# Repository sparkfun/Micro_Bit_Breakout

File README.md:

SparkFun micro:bit Breakout Board
========================================

[*Micro Bit Breakout (BOB-16446)*](https://www.sparkfun.com/products/16446)

The [Micro Bit Breakout](https://www.sparkfun.com/products/16446) is a board that connects to the BBC micro:bit and breaks out all 21 GPIO pins, power, and ground to a 0.1" header. It expands the capabilities of the micro:bit by providing access to more pins and allowing for connections to the I<sup>2</sup>C and SPI buses. It additionally has two qwiic connectors to take advantage of the Qwiic I2C protocols. 

The micro:bit Breakout Board is also [available without pre-soldered headers](https://www.sparkfun.com/products/16445). More information can be found in the [Micro Bit Breakout Hookup Guide](https://learn.sparkfun.com/tutorials/microbit-breakout-board-hookup-guide).

Repository Contents
-------------------

* **/Documentation** - Data sheets, additional product information
* **/Firmware** - Example code used with micro:bit and the breakout board. MakeCode examples are compiled HEX codes and can be modified once they are imported into MakeCode editor. MicroPython examples can also be modified in a Python editor like Mu.
* **/Hardware** - Eagle design files (.brd, .sch)
* **/Production** - Production panel files (.brd)

Documentation
--------------
* Tutorials
  * **[Hookup Guide](https://learn.sparkfun.com/tutorials/microbit-breakout-board-hookup-guide)** - Basic hookup guide.
  * **[SparkFun Inventor's Kit for micro:bit Experiment Guide](https://learn.sparkfun.com/tutorials/sparkfun-inventors-kit-for-microbit-experiment-guide)** - Experiment Guide
  * **[micro:bit Educator Lab Pack Experiment Guide](https://learn.sparkfun.com/tutorials/microbit-educator-lab-pack-experiment-guide)** - Experiment Guide for the Lab Pack
  * **[Getting Started with MicroPython and the SparkFun Inventor's Kit for micro:bit](https://learn.sparkfun.com/tutorials/getting-started-with-micropython-and-the-sparkfun-inventors-kit-for-microbit)** Experiment Guide in MicroPython
* **[SparkFun Fritzing repo](https://github.com/sparkfun/Fritzing_Parts)** - Fritzing diagrams for SparkFun products.
* **[SparkFun 3D Model repo](https://github.com/sparkfun/3D_Models)** - 3D models of SparkFun products. 
* **[SparkFun Graphical Datasheets](https://github.com/sparkfun/Graphical_Datasheets)** -Graphical Datasheets for various SparkFun products.

Product Versions
----------------
* [Micro Bit Breakout v0.3 (BOB-16446)](https://www.sparkfun.com/products/16446) - v0.3
* [Micro Bit Breakout (Without Headers) v0.3 (BOB-16445)](https://www.sparkfun.com/products/16445) - v0.3
* [Micro Bit Breakout v0.2 (BOB-13988)](https://www.sparkfun.com/products/13988) - Initial release
* [Micro Bit Breakout v0.2 with Headers (BOB-13989)](https://www.sparkfun.com/products/13989) - Initial release

Version History
---------------
* [v03](https://github.com/sparkfun/Micro_Bit_Breakout/tree/v03) - v0.3 Changed connector to SMD, added Qwiic connectors
* [v02](https://github.com/sparkfun/Micro_Bit_Breakout/tree/v02) - v0.2 Increased board width, changed pin numbers
* [v01](https://github.com/sparkfun/Micro_Bit_Breakout/tree/v01) - v0.1 Hardware release

License Information
-------------------

This product is _**open source**_! 

Please review the LICENSE.md file for license information. 

If you have any questions or concerns on licensing, please contact techsupport@sparkfun.com.

Distributed as-is; no warranty is given.

- Your friends at SparkFun.

_<COLLABORATION CREDIT>_

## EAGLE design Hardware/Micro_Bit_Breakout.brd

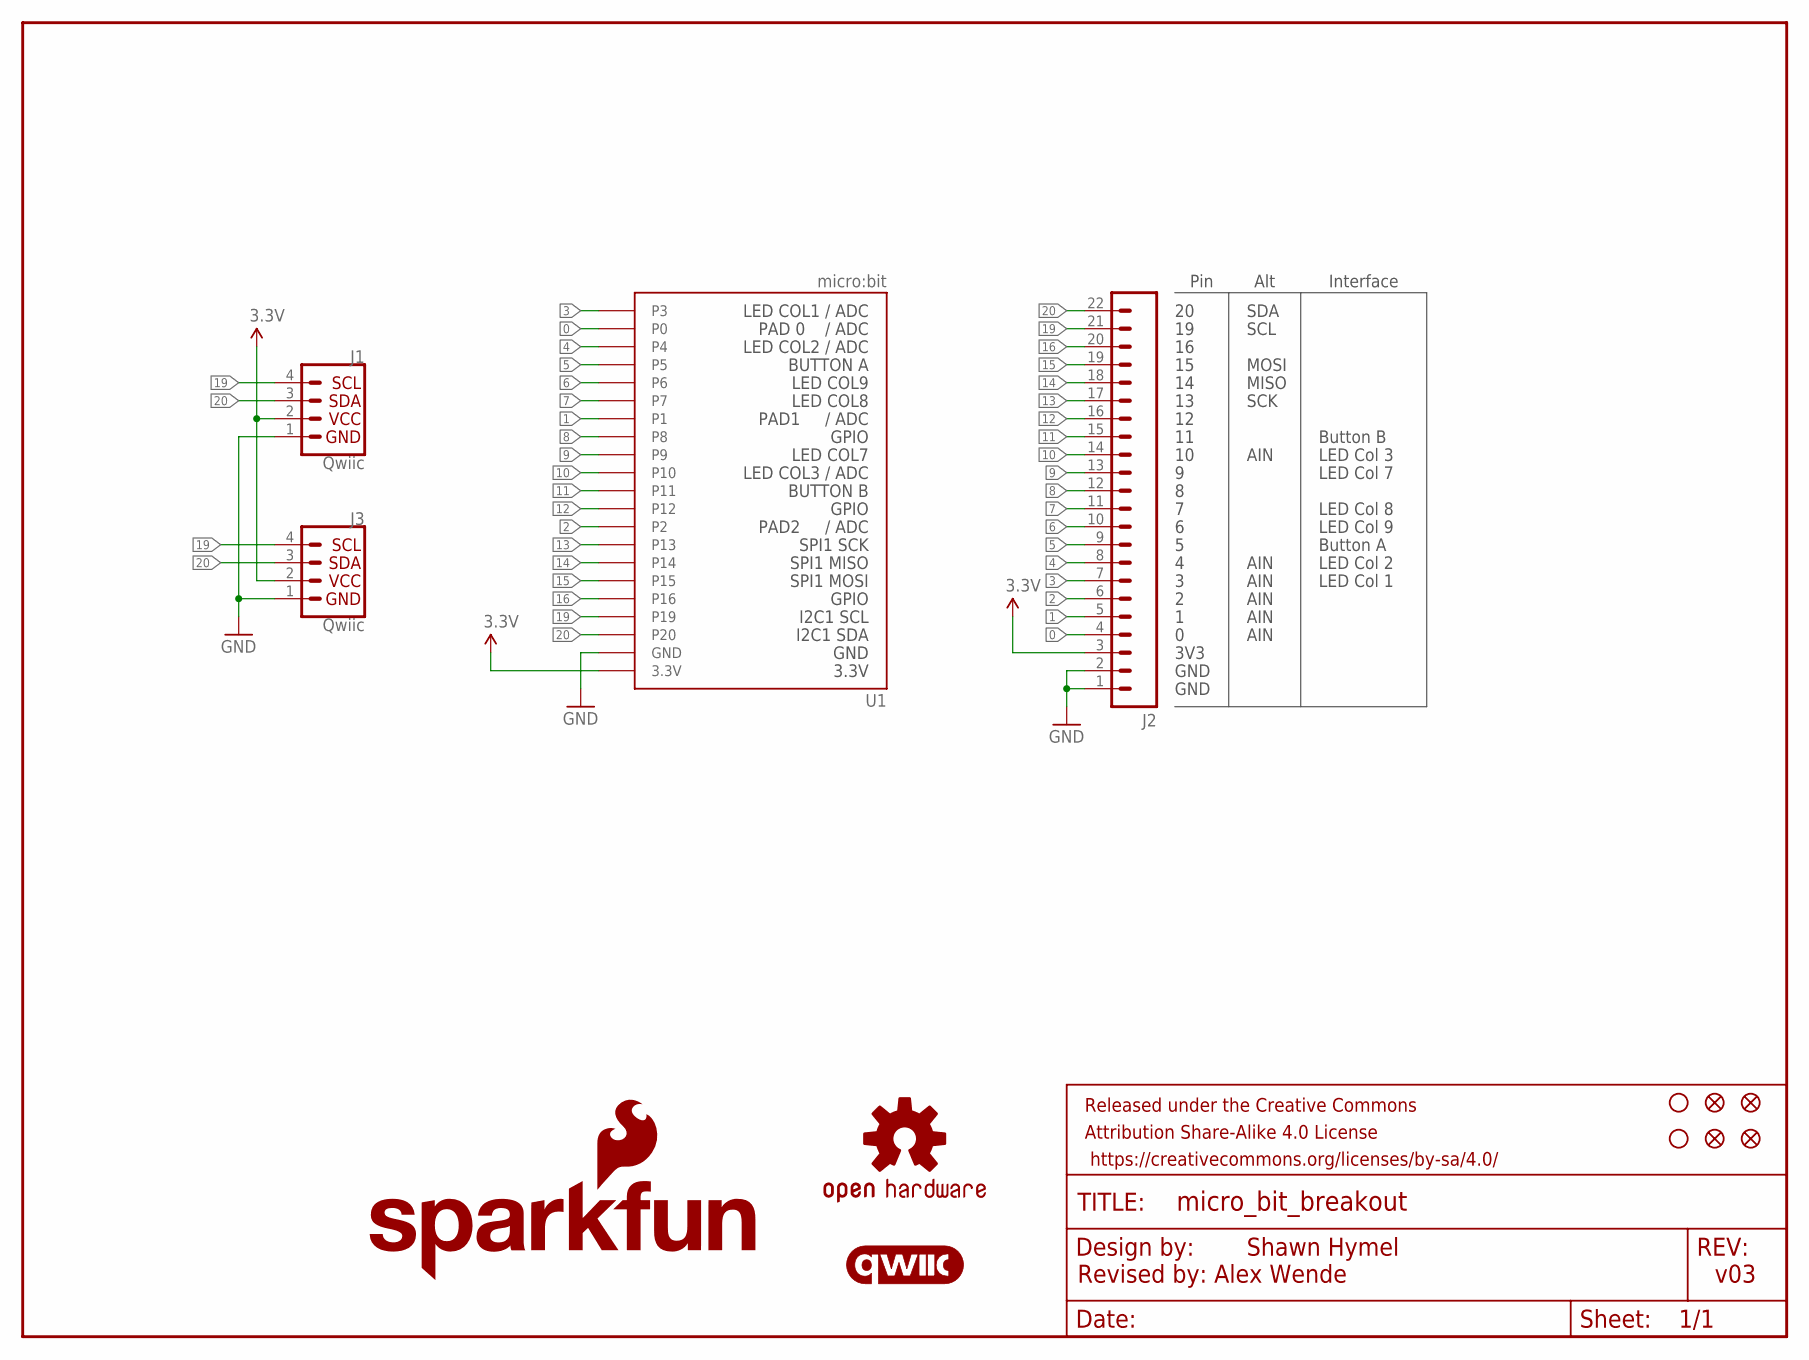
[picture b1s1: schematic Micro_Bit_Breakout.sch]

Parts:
FD1, FD2, FD3, FD4: FIDUCIAL1X2; FIDUCIAL-1X2
FRAME1: FRAME-LETTER; CREATIVE_COMMONS
H1, H2: STAND-OFF
J1, J3: Qwiic; JST04_1MM_VERT
J2: CONN_22_NOSILK; 1X22_NOSILK
LOGO1: QWIIC_LOGO_5MM; QWIIC_5MM
LOGO2: SFE_LOGO_NAME_FLAME.1_INCH; SFE_LOGO_NAME_FLAME_.1
LOGO3: OSHW-LOGOM; OSHW-LOGO-M
U1: micro:bit; MICRO:BIT-RA_SMD

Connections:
0: J2.4, U1.P$2 (P0), U1.P$3 (P0), U1.P$4 (P0), U1.P$5 (P0)
1: J2.5, U1.P$10 (P1), U1.P$11 (P1), U1.P$12 (P1), U1.P$13 (P1)
2: J2.6, U1.P$19 (P2), U1.P$20 (P2), U1.P$21 (P2), U1.P$22 (P2)
3: J2.7, U1.P$1 (P3)
3.3V: J1.2, J2.3, J3.2, U1.P$27 (3.3V), U1.P$28 (3.3V), U1.P$29 (3.3V), U1.P$30 (3.3V), U1.P$31 (3.3V), U1.P$32 (3.3V)
4: J2.8, U1.P$6 (P4)
5: J2.9, U1.P$7 (P5)
6: J2.10, U1.P$8 (P6)
7: J2.11, U1.P$9 (P7)
8: J2.12, U1.P$14 (P8)
9: J2.13, U1.P$15 (P9)
10: J2.14, U1.P$16 (P10)
11: J2.15, U1.P$17 (P11)
12: J2.16, U1.P$18 (P12)
13: J2.17, U1.P$23 (P13)
14: J2.18, U1.P$24 (P14)
15: J2.19, U1.P$25 (P15)
16: J2.20, U1.P$26 (P16)
19: J1.4, J2.21, J3.4, U1.P$33 (P19)
20: J1.3, J2.22, J3.3, U1.P$34 (P20)
GND: J1.1, J2.1, J2.2, J3.1, U1.P$35 (GND), U1.P$36 (GND), U1.P$37 (GND), U1.P$38 (GND), U1.P$39 (GND), U1.P$40 (GND)

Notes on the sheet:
Shawn Hymel
v03
GND
3V3
SCL
SDA
SCK
MISO
MOSI
AIN
Button B
LED Col 3
LED Col 7
LED Col 8
LED Col 9
LED Col 2
Button A
LED Col 1
Pin
Alt
Interface
Revised by: Alex Wende

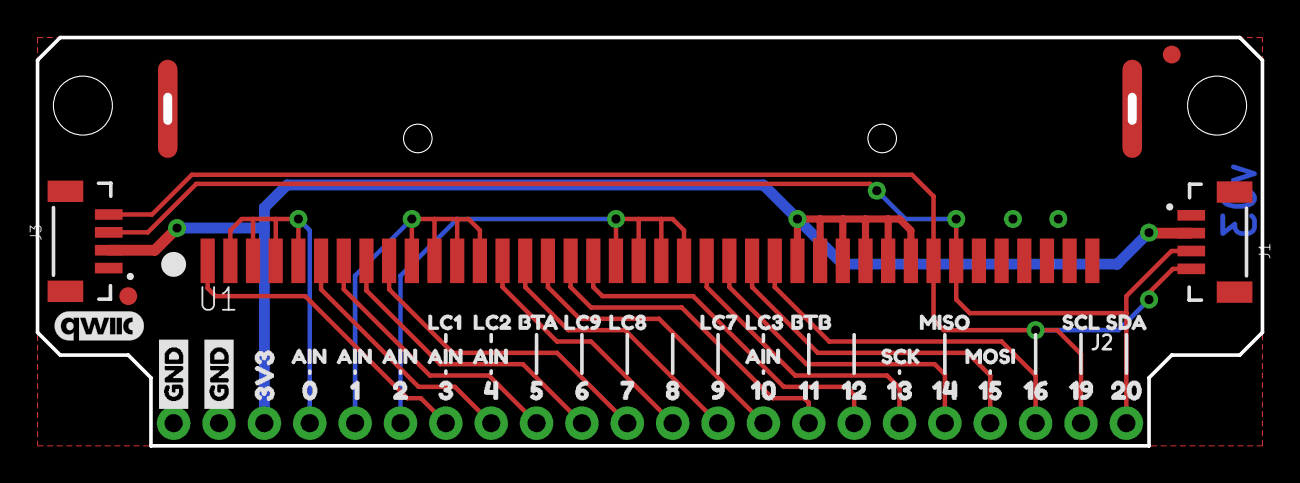
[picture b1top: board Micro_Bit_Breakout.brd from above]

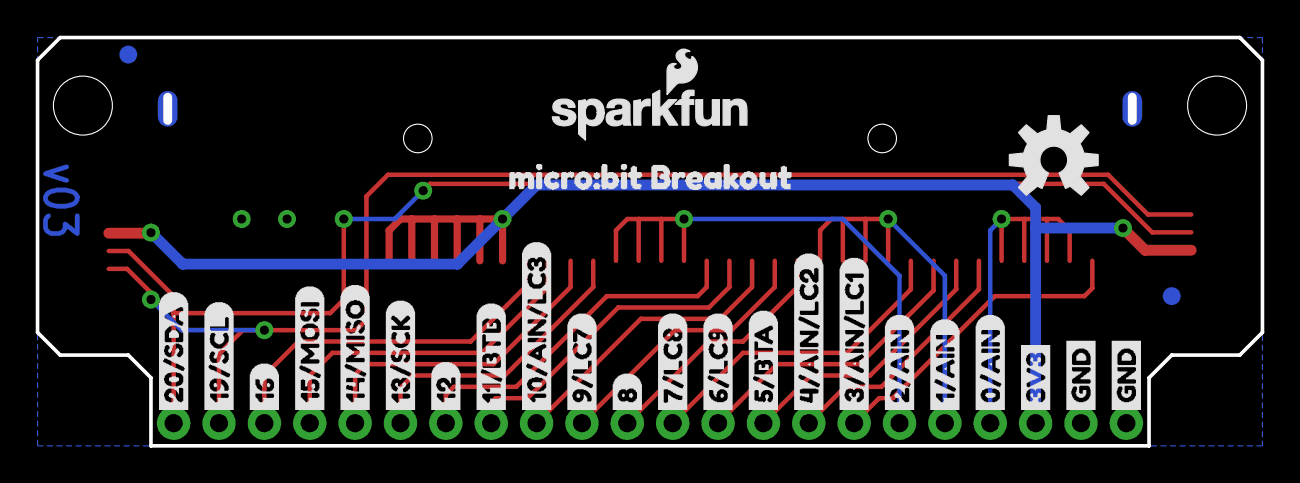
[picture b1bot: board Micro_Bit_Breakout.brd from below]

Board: 2 copper layers, 68.3 x 22.6 mm, 78 parts (27 on the bottom side), 21 nets.

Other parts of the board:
U$1, U$22, U$23, U$24: GND0
U$2: 20#SDA20
U$3: 19#SCL19
U$4, U$43: 1618
U$5: 15#MOSI17
U$6: 14#MISO16
U$7: 13#SCK15
U$8, U$39: 1214
U$9: 11#BTB13
U$10: 10#AIN#LC312
U$11: 9#LC711
U$12, U$35: 810
U$13: 7#LC89
U$14: 6#LC98
U$15: 5#BTA7
U$16: 4#AIN#LC26
U$17: 3#AIN#LC15
U$18: 2#AIN4
U$19: 1#AIN3
U$20: 0#AIN2
U$21, U$26: 3V31
U$25: MICRO#BIT_BREAKOUT0
U$27: 02
U$28: 13
U$29: 24
U$30: 35
U$31: 46
U$32: 57
U$33: 68
U$34: 79
U$36: 911
U$37: 1012
U$38: 1113
U$40: 1315
U$41: 1416
U$42: 1517
U$44: 1919
U$45: 2020
U$46, U$47, U$48, U$49, U$50, U$51: AIN0
U$52: LC11
U$53: LC22
U$54: BTA3
U$55: LC95
U$56: LC86
U$57: LC77
U$58: LC38
U$59: BTB4
U$60: SCK9
U$61: MISO10
U$62: MOSI11
U$63: SCL12
U$64: SDA13

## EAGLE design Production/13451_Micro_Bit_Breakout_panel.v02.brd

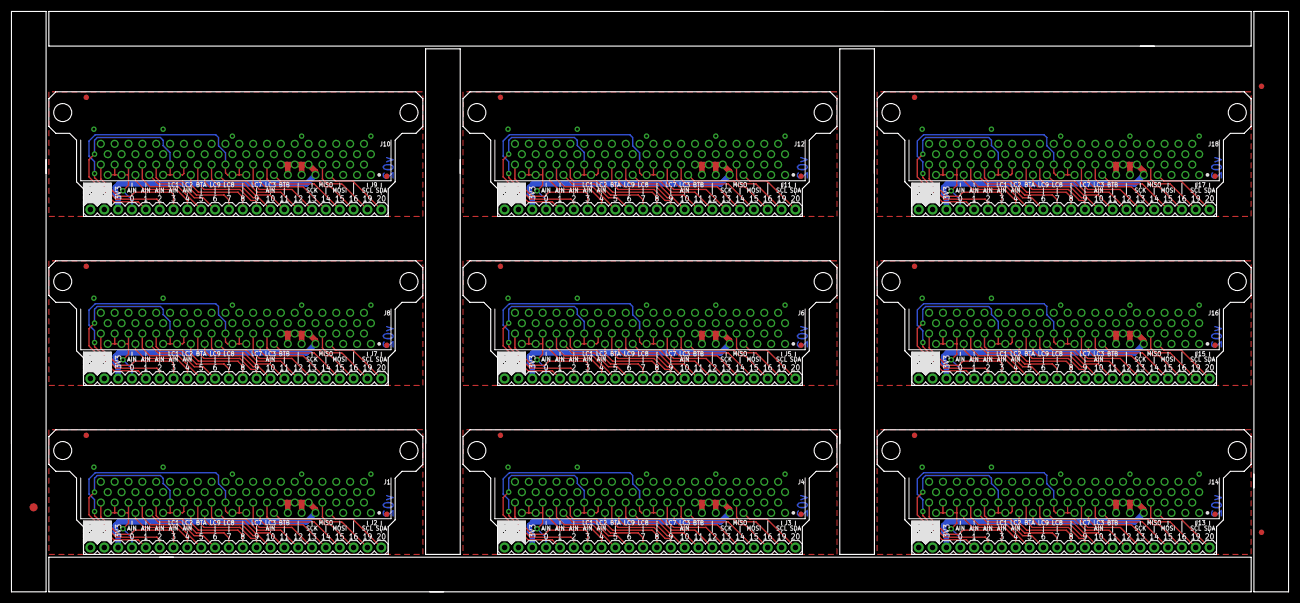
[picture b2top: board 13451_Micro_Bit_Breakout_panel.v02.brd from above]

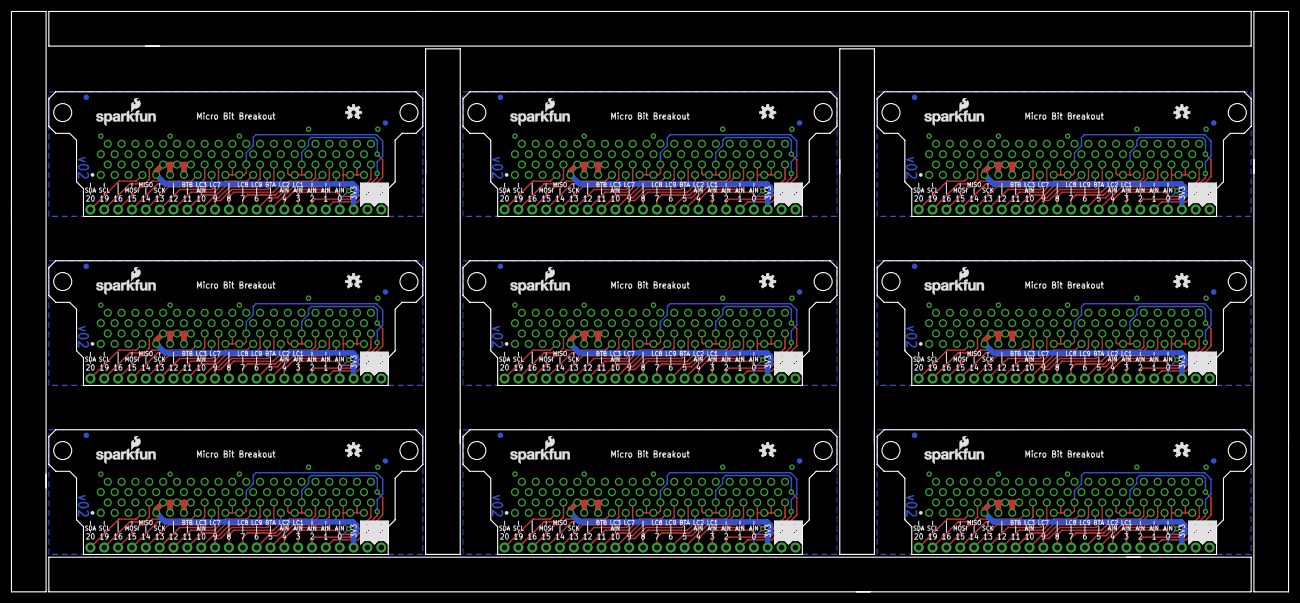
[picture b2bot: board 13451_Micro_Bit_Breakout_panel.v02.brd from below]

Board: 2 copper layers, 234.2 x 106.4 mm, 111 parts (45 on the bottom side), 189 nets.

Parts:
E$1: FIDUCIAL-1.5X3
E$9, E$10: FIDUCIAL-1X2
FD1, FD2, FD3, FD4, FD5, FD6, FD7, FD8, FD9, FD10, FD11, FD12, FD13, FD14, FD15, FD16, FD17, FD18, FD19, FD20, FD21, FD22, FD23, FD24, FD25, FD26, FD27, FD28, FD29, FD30, FD31, FD32, FD33, FD34, FD35, FD36: FIDUCIAL1X2; FIDUCIAL-1X2
H1, H2, H3, H4, H5, H6, H7, H8, H9, H10, H11, H12, H13, H14, H15, H16, H17, H18: STAND-OFF
J1, J4, J6, J8, J10, J12, J14, J16, J18: EDGE-80PTH-RA; VEC-127-080-R
J2, J3, J5, J7, J9, J11, J13, J15, J17: M22PTH; 1X22
LOGO1, LOGO3, LOGO5, LOGO7, LOGO9, LOGO11, LOGO13, LOGO15, LOGO17: OSHW-LOGOS; OSHW-LOGO-S
LOGO2, LOGO4, LOGO6, LOGO8, LOGO10, LOGO12, LOGO14, LOGO16, LOGO18: SFE_LOGO_NAME_FLAME.1_INCH; SFE_LOGO_NAME_FLAME_.1
U$1, U$2, U$3, U$4, U$5, U$6, U$7, U$8, U$9, U$10, U$11, U$12, U$13, U$14, U$15, U$16, U$17, U$18: NEGASILK_MICRO_BIT_BREAKOUT

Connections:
0: J1.A36, J1.A37, J1.A38, J1.A39, J2.4
1: J1.A28, J1.A29, J1.A30, J1.A31, J2.5
2: J1.A19, J1.A20, J1.A21, J1.A22, J2.6
3: J1.A40, J2.7
3.3V: J1.A9, J1.A10, J1.A11, J1.A12, J1.A13, J1.A14, J2.3
3.3V1: J3.3, J4.A9, J4.A10, J4.A11, J4.A12, J4.A13, J4.A14
3.3V2: J5.3, J6.A9, J6.A10, J6.A11, J6.A12, J6.A13, J6.A14
3.3V3: J7.3, J8.A9, J8.A10, J8.A11, J8.A12, J8.A13, J8.A14
3.3V4: J9.3, J10.A9, J10.A10, J10.A11, J10.A12, J10.A13, J10.A14
3.3V5: J11.3, J12.A9, J12.A10, J12.A11, J12.A12, J12.A13, J12.A14
3.3V6: J13.3, J14.A9, J14.A10, J14.A11, J14.A12, J14.A13, J14.A14
3.3V7: J15.3, J16.A9, J16.A10, J16.A11, J16.A12, J16.A13, J16.A14
3.3V8: J17.3, J18.A9, J18.A10, J18.A11, J18.A12, J18.A13, J18.A14
4: J1.A35, J2.8
5: J1.A34, J2.9
6: J1.A33, J2.10
7: J1.A32, J2.11
8: J1.A27, J2.12
9: J1.A26, J2.13
10: J1.A25, J2.14
11: J1.A24, J2.15
12: J1.A23, J2.16
13: J1.A18, J2.17
14: J1.A17, J2.18
15: J1.A16, J2.19
16: J1.A15, J2.20
17: J3.22, J4.A7
18: J3.21, J4.A8
19: J1.A8, J2.21
20: J1.A7, J2.22
21: J3.20, J4.A15
22: J3.19, J4.A16
23: J3.18, J4.A17
24: J3.17, J4.A18
25: J3.6, J4.A19, J4.A20, J4.A21, J4.A22
26: J3.16, J4.A23
27: J3.15, J4.A24
28: J3.14, J4.A25
29: J3.13, J4.A26
30: J3.12, J4.A27
31: J3.5, J4.A28, J4.A29, J4.A30, J4.A31
32: J3.11, J4.A32
33: J3.10, J4.A33
34: J3.9, J4.A34
35: J3.8, J4.A35
36: J3.4, J4.A36, J4.A37, J4.A38, J4.A39
37: J3.7, J4.A40
38: J5.22, J6.A7
39: J5.21, J6.A8
40: J5.20, J6.A15
41: J5.19, J6.A16
42: J5.18, J6.A17
43: J5.17, J6.A18
44: J5.6, J6.A19, J6.A20, J6.A21, J6.A22
45: J5.16, J6.A23
46: J5.15, J6.A24
47: J5.14, J6.A25
48: J5.13, J6.A26
49: J5.12, J6.A27
50: J5.5, J6.A28, J6.A29, J6.A30, J6.A31
51: J5.11, J6.A32
52: J5.10, J6.A33
53: J5.9, J6.A34
54: J5.8, J6.A35
55: J5.4, J6.A36, J6.A37, J6.A38, J6.A39
56: J5.7, J6.A40
57: J7.22, J8.A7
58: J7.21, J8.A8
59: J7.20, J8.A15
60: J7.19, J8.A16
61: J7.18, J8.A17
62: J7.17, J8.A18
63: J7.6, J8.A19, J8.A20, J8.A21, J8.A22
64: J7.16, J8.A23
65: J7.15, J8.A24
66: J7.14, J8.A25
67: J7.13, J8.A26
68: J7.12, J8.A27
69: J7.5, J8.A28, J8.A29, J8.A30, J8.A31
70: J7.11, J8.A32
71: J7.10, J8.A33
72: J7.9, J8.A34
73: J7.8, J8.A35
74: J7.4, J8.A36, J8.A37, J8.A38, J8.A39
75: J7.7, J8.A40
76: J9.22, J10.A7
77: J9.21, J10.A8
78: J9.20, J10.A15
79: J9.19, J10.A16
80: J9.18, J10.A17
81: J9.17, J10.A18
82: J9.6, J10.A19, J10.A20, J10.A21, J10.A22
83: J9.16, J10.A23
84: J9.15, J10.A24
85: J9.14, J10.A25
86: J9.13, J10.A26
87: J9.12, J10.A27
88: J9.5, J10.A28, J10.A29, J10.A30, J10.A31
89: J9.11, J10.A32
90: J9.10, J10.A33
91: J9.9, J10.A34
92: J9.8, J10.A35
93: J9.4, J10.A36, J10.A37, J10.A38, J10.A39
94: J9.7, J10.A40
95: J11.22, J12.A7
96: J11.21, J12.A8
97: J11.20, J12.A15
98: J11.19, J12.A16
99: J11.18, J12.A17
100: J11.17, J12.A18
101: J11.6, J12.A19, J12.A20, J12.A21, J12.A22
102: J11.16, J12.A23
103: J11.15, J12.A24
104: J11.14, J12.A25
105: J11.13, J12.A26
106: J11.12, J12.A27
107: J11.5, J12.A28, J12.A29, J12.A30, J12.A31
108: J11.11, J12.A32
109: J11.10, J12.A33
110: J11.9, J12.A34
111: J11.8, J12.A35
112: J11.4, J12.A36, J12.A37, J12.A38, J12.A39
113: J11.7, J12.A40
114: J13.22, J14.A7
115: J13.21, J14.A8
116: J13.20, J14.A15
117: J13.19, J14.A16
118: J13.18, J14.A17
119: J13.17, J14.A18
120: J13.6, J14.A19, J14.A20, J14.A21, J14.A22
121: J13.16, J14.A23
122: J13.15, J14.A24
123: J13.14, J14.A25
124: J13.13, J14.A26
125: J13.12, J14.A27
126: J13.5, J14.A28, J14.A29, J14.A30, J14.A31
127: J13.11, J14.A32
128: J13.10, J14.A33
129: J13.9, J14.A34
130: J13.8, J14.A35
131: J13.4, J14.A36, J14.A37, J14.A38, J14.A39
132: J13.7, J14.A40
133: J15.22, J16.A7
134: J15.21, J16.A8
135: J15.20, J16.A15
136: J15.19, J16.A16
137: J15.18, J16.A17
138: J15.17, J16.A18
139: J15.6, J16.A19, J16.A20, J16.A21, J16.A22
140: J15.16, J16.A23
141: J15.15, J16.A24
142: J15.14, J16.A25
143: J15.13, J16.A26
144: J15.12, J16.A27
145: J15.5, J16.A28, J16.A29, J16.A30, J16.A31
146: J15.11, J16.A32
147: J15.10, J16.A33
148: J15.9, J16.A34
149: J15.8, J16.A35
150: J15.4, J16.A36, J16.A37, J16.A38, J16.A39
151: J15.7, J16.A40
152: J17.22, J18.A7
153: J17.21, J18.A8
154: J17.20, J18.A15
155: J17.19, J18.A16
156: J17.18, J18.A17
157: J17.17, J18.A18
158: J17.6, J18.A19, J18.A20, J18.A21, J18.A22
159: J17.16, J18.A23
160: J17.15, J18.A24
161: J17.14, J18.A25
162: J17.13, J18.A26
163: J17.12, J18.A27
164: J17.5, J18.A28, J18.A29, J18.A30, J18.A31
165: J17.11, J18.A32
166: J17.10, J18.A33
167: J17.9, J18.A34
168: J17.8, J18.A35
169: J17.4, J18.A36, J18.A37, J18.A38, J18.A39
170: J17.7, J18.A40
GND: J1.A1, J1.A2, J1.A3, J1.A4, J1.A5, J1.A6, J2.1, J2.2
GND1: J3.1, J3.2, J4.A1, J4.A2, J4.A3, J4.A4, J4.A5, J4.A6
GND2: J5.1, J5.2, J6.A1, J6.A2, J6.A3, J6.A4, J6.A5, J6.A6
GND3: J7.1, J7.2, J8.A1, J8.A2, J8.A3, J8.A4, J8.A5, J8.A6
GND4: J9.1, J9.2, J10.A1, J10.A2, J10.A3, J10.A4, J10.A5, J10.A6
GND5: J11.1, J11.2, J12.A1, J12.A2, J12.A3, J12.A4, J12.A5, J12.A6
GND6: J13.1, J13.2, J14.A1, J14.A2, J14.A3, J14.A4, J14.A5, J14.A6
GND7: J15.1, J15.2, J16.A1, J16.A2, J16.A3, J16.A4, J16.A5, J16.A6
GND8: J17.1, J17.2, J18.A1, J18.A2, J18.A3, J18.A4, J18.A5, J18.A6

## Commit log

2016-07-12 Changed text ratio
2016-07-15 Moved brd outline down
2016-07-18 Changed layout to have pin numbers in order. Added prettier silk.
2016-07-19 Added dimension for origin to end of edge connector. Added pin 1 dot in silk for edge connector.
2016-07-20 Changed 3V3 net to 3.3V symbol
2016-08-10 Changed pins to match new micro:bit pinout. Updated to v10. Ready for review.
2016-08-15 Moved top up 0.1 inches. Added bottom fiducials. Added dimensions note for measurements.
2016-10-26 Updated readme again
2016-10-27 Panel
2017-05-05 Added PDF schematic
2017-05-05 Removed lock files
2019-01-08 micro:Bit and Breakout Example Code HEX files
    Add compiled MakeCode example code used in with micro:bit and breakout board
2019-01-09 Add MicroPython Examples
2020-03-16 v03
    -Replaced micro:bit connector with SMD version
    -Replaced silk with buzzard labels
2020-03-18 Added ground vias
2020-03-18 Design Review Changes
    - Changed schematic text to vector font
    - Increased 3.3V trace width
2020-03-19 Added Qwiic Connectors
    Added virtical qwiic connectors
2020-03-19 Update Micro_Bit_Breakout.brd
    Moved the Qwiic logo
2021-06-18 Update README.md
    Updating versions to reflect v03 release

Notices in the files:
parts and their libraries:
SparkFun-Aesthetics: Licensing: Creative Commons ShareAlike 4.0 International - https://creativecommons.org/licenses/by-sa/4.0
SparkFun-Aesthetics: Released under the Creative Commons Attribution Share-Alike 4.0 License
SparkFun-Aesthetics: https://creativecommons.org/licenses/by-sa/4.0
